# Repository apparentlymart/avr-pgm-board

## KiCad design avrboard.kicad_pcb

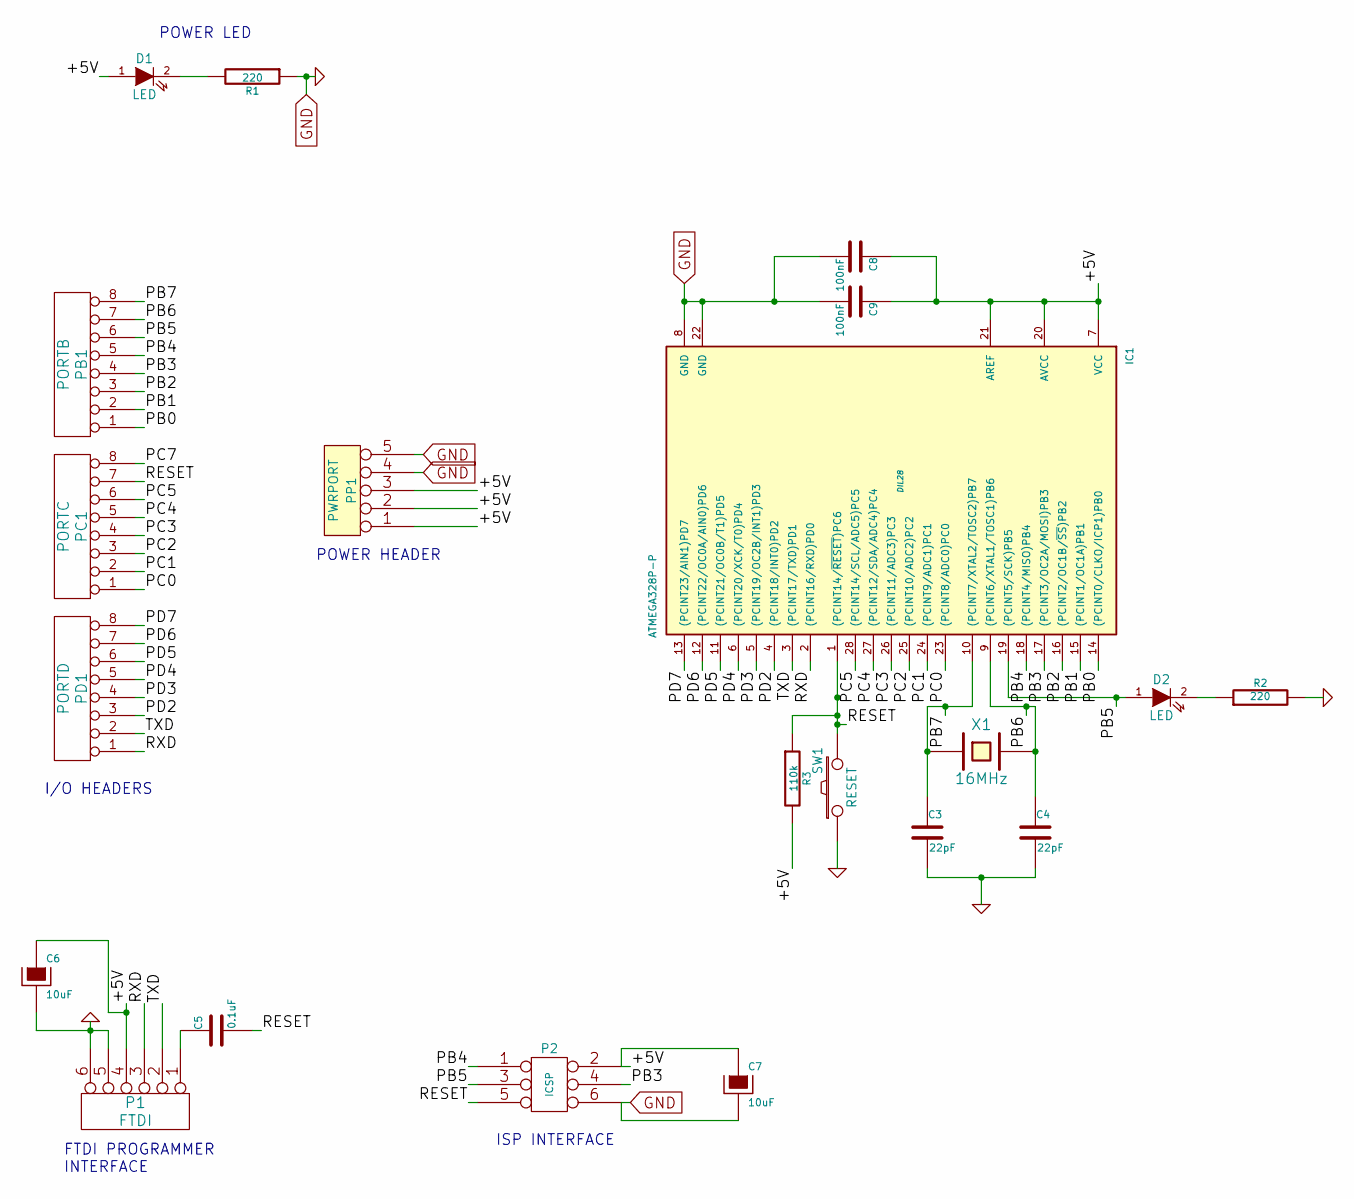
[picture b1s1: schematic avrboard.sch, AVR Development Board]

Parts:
C3, C4: 22pF
C5: 0.1uF
C6, C7: 10uF
C8, C9: 100nF
D1, D2: LED
IC1: ATMEGA328P-P; DIL28
P1: FTDI
P2: ICSP
PB1: PORTB
PC1: PORTC
PD1: PORTD
PP1: PWRPORT
R1, R2: 220
R3: 110k
SW1: RESET
X1: 16MHz

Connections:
/+5V: C6.1, C7.1, C8.1, C9.1, D1.1 (A), IC1.7 (VCC), IC1.20 (AVCC), IC1.21 (AREF), P1.4, P2.2, PP1.1, PP1.2, PP1.3, R3.2
/PB0: IC1.14 ((PCINT0/CLKO/ICP1)PB0), PB1.1
/PB1: IC1.15 ((PCINT1/OC1A)PB1), PB1.2
/PB2: IC1.16 ((PCINT2/OC1B/~SS~)PB2), PB1.3
/PB3: IC1.17 ((PCINT3/OC2A/MOSI)PB3), P2.4, PB1.4
/PB4: IC1.18 ((PCINT4/MISO)PB4), P2.1, PB1.5
/PB5: D2.1 (A), IC1.19 ((PCINT5/SCK)PB5), P2.3, PB1.6
/PB6: C4.1, IC1.9 ((PCINT6/XTAL1/TOSC1)PB6), PB1.7, X1.2
/PB7: C3.1, IC1.10 ((PCINT7/XTAL2/TOSC2)PB7), PB1.8, X1.1
/PC0: IC1.23 ((PCINT8/ADC0)PC0), PC1.1
/PC1: IC1.24 ((PCINT9/ADC1)PC1), PC1.2
/PC2: IC1.25 ((PCINT10/ADC2)PC2), PC1.3
/PC3: IC1.26 ((PCINT11/ADC3)PC3), PC1.4
/PC4: IC1.27 ((PCINT12/SDA/ADC4)PC4), PC1.5
/PC5: IC1.28 ((PCINT14/SCL/ADC5)PC5), PC1.6
/PC7: PC1.8
/PD2: IC1.4 ((PCINT18/INT0)PD2), PD1.3
/PD3: IC1.5 ((PCINT19/OC2B/INT1)PD3), PD1.4
/PD4: IC1.6 ((PCINT20/XCK/T0)PD4), PD1.5
/PD5: IC1.11 ((PCINT21/OC0B/T1)PD5), PD1.6
/PD6: IC1.12 ((PCINT22/OC0A/AIN0)PD6), PD1.7
/PD7: IC1.13 ((PCINT23/AIN1)PD7), PD1.8
/RESET: C5.2, IC1.1 ((PCINT14/~RESET~)PC6), P2.5, PC1.7, R3.1, SW1.2
/RXD: IC1.2 ((PCINT16/RXD)PD0), P1.3, PD1.1
/TXD: IC1.3 ((PCINT17/TXD)PD1), P1.2, PD1.2
GND: C3.2, C4.2, C6.2, C7.2, C8.2, C9.2, IC1.8 (GND), IC1.22 (GND), P1.5, P1.6, P2.6, PP1.4, PP1.5, R1.1, R2.2, SW1.1
unnamed: C5.1, P1.1
unnamed: D1.2 (K), R1.2
unnamed: D2.2 (K), R2.1

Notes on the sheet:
POWER LED
FTDI PROGRAMMER INTERFACE
I/O HEADERS
POWER HEADER
ISP INTERFACE

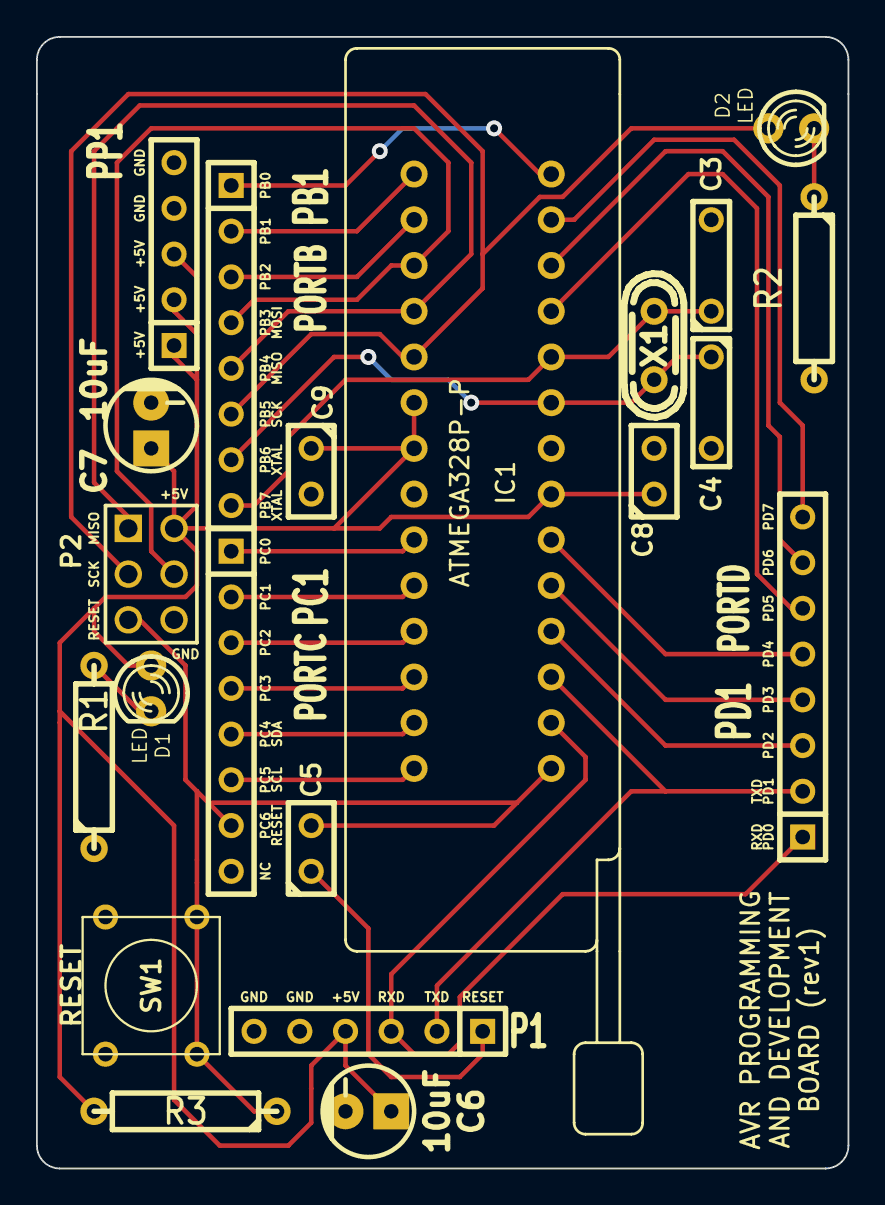
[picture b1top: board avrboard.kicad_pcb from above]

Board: 2 copper layers, 45.1 x 62.9 mm, 21 parts (0 on the bottom side), 28 nets.

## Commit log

2014-04-20 Initial Import
2014-04-20 Route to the the RESET pin via the back of the board.
    This allows the RESET signal to hope over the serial TX/RX signals.
2014-04-20 Unhide the back copper layer.
2014-04-20 Finish routing the PCB traces.
    Got a little ugly towards the end to get the traces to the programming
    headers, but not too bad. Might revise later.
2014-04-20 Connect AREF to +5V.
    No sensible way to route AREF, so for now the compromise is to just route
    it to +5V so the ADC can be *usable* when configured to use an external
    voltage source (e.g. for testing after programming) while not being
    particularly accurate (since this is going to be noisy.)
    Given that the primary purpose of this board is programming and then
    post-programming brief testing, with the chip ultimately ending up in
2014-04-20 Remove the power regulator from the design.
    Since this board is primarily for programming, it's fine to just get
    power from the ICSP or FTDI headers in most cases, which should already
    be regulated to 5V.
    There was nowhere in the design for the power barrel jack to go anyway,
    so this saves a little more space and also allows the ICSP header to move
    closer to the SPI pins and thus fix some of the more awkward routes
2014-04-20 More port labels and some track routing adjustments.
2014-04-20 Move the PORTB headers to the other side of the chip.
    The routing is less crazy this way, since many of the port B pins are on
    that side, and the power and port B headers can both fit together on that
    side.
2014-04-20 Clean up the silkscreen and remove some "bays" from the ground plane.
2014-04-21 Move the FTDI socket over to increase clearance from the ZIF lever.
2014-04-21 Add board outline.
2014-04-21 Correct the size of the ZIF socket.
    The footprint was 75mil too short.
2014-04-21 Remove one of the fill keepouts to repair the ground plane.
2014-04-21 Prepare plotter settings for Gerber export.
2014-04-21 Further silkscreen layout tweaking.
    Some captions were overlapping. Now none are overlapping.
2014-04-21 Include a caption on the back silkscreen.
    OSH Park refuses to accept an empty back silkscreen layer, for some
    reason.
2014-04-21 Remove a redundant "GND" label from an earlier version.
2014-04-21 Update plotter settings for OSH Park manufacturing.
